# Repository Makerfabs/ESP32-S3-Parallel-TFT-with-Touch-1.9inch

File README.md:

# ESP32-S3-Parallel-TFT-with-Touch-1.9inch

```
/* 
    Version:      V1.1
    Author:       Ricardo
    Create Date:  2023/4/27
*/
```

# Makerfabs

[Makerfabs home page](https://www.makerfabs.com/)

[Makerfabs Wiki](https://wiki.makerfabs.com/)

## Intruduce

Product Link:[ESP32-S3 Parallel TFT with Touch 1.9"](https://www.makerfabs.com/matouch-esp32-s3-parallel-tft-with-touch-1-9-inch.html?search=Esp32%20s3%201.9)

Wiki Link : [ESP32-S3 Parallel 1.9 TFT with Touch](https://wiki.makerfabs.com/ESP32_S3_Parallel_1.9_TFT_with_Touch.html)

IoT applications have a certain demand for the 1.9" screen. The small screen brings higher cost performance and utilization rate. Its main control chip adopts ESP32-S3R8 Dual-core LX7 microcontroller, it features Wifi/ WiFi& Bluetooth 5.0 + BT mesh.

At the same time, it supports battery and USB power supply methods, which brings many possibilities to its application. At the same time, it has a TF card, which can store and transfer sensor data. Also there 2 expansion connectors, with UART/ADC. The colorful display resolution is 320*170, with capacitive touch, which could be a proper solution for IoT applications.

## Features

- Controller: ESP32-S3
- Wireless: WiFi& Bluetooth 5.0
- LCD: 1.9", 320x170 resolution, driver ST7789V2
- LCD interface: 8 bit 8080
- Touch Panel Driver: CST816D
- USB: USB Native, Type-C
- Power Supply: USB Type-C 5.0V(4.0V~5.25V); 3.7V Lipo battery
- Button: Flash button and reset button
- Expansion interface: 2 (UART/ADC)
- MicroSD
- Arduino support
- MicroPython support: Yes
- Operation temperature: -40℃ to +85℃

## Usage

related library versions

- Use type-c use cable connect USB-TTL to PC.
- Select "ESP32-S3 DEV Module"
- Select PSRAM "OPI PSRAM"

"mf_Lvgl" library is modified from Lvgl library (version 8.3.2). 

Please unzip "lib/mf_Lvgl.zip"."TouchLib" and copy to arduino library directory.

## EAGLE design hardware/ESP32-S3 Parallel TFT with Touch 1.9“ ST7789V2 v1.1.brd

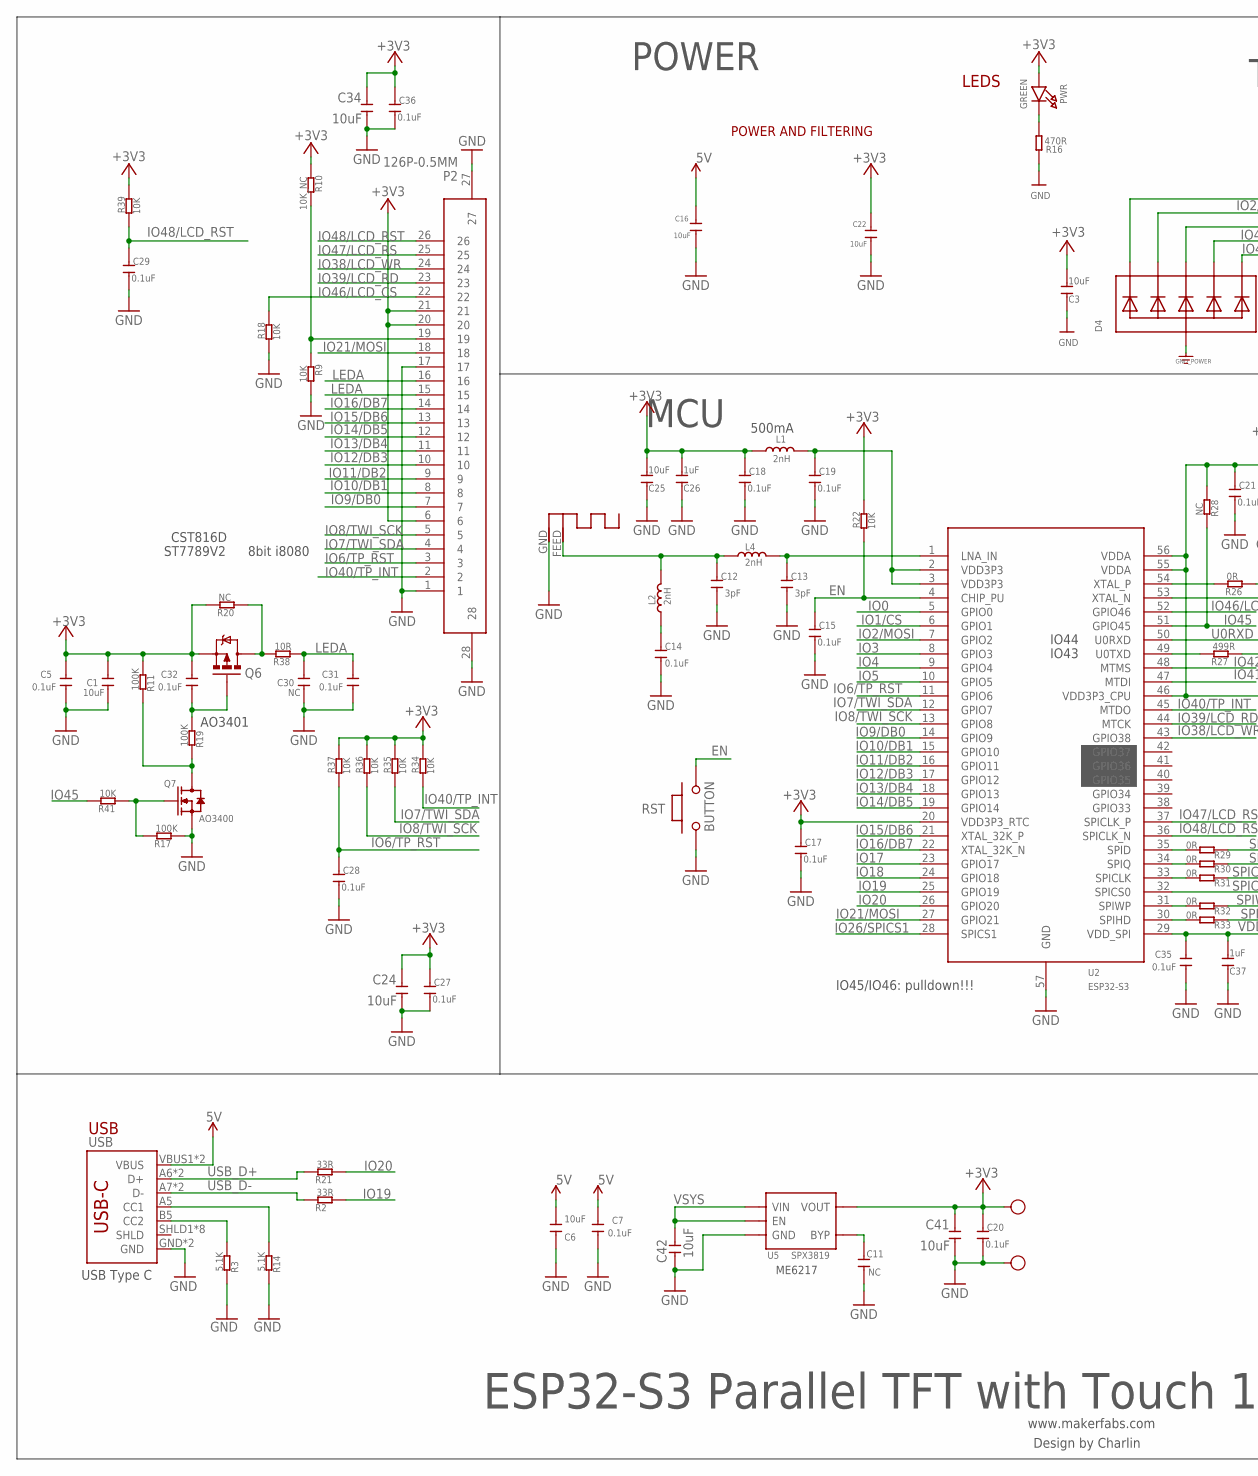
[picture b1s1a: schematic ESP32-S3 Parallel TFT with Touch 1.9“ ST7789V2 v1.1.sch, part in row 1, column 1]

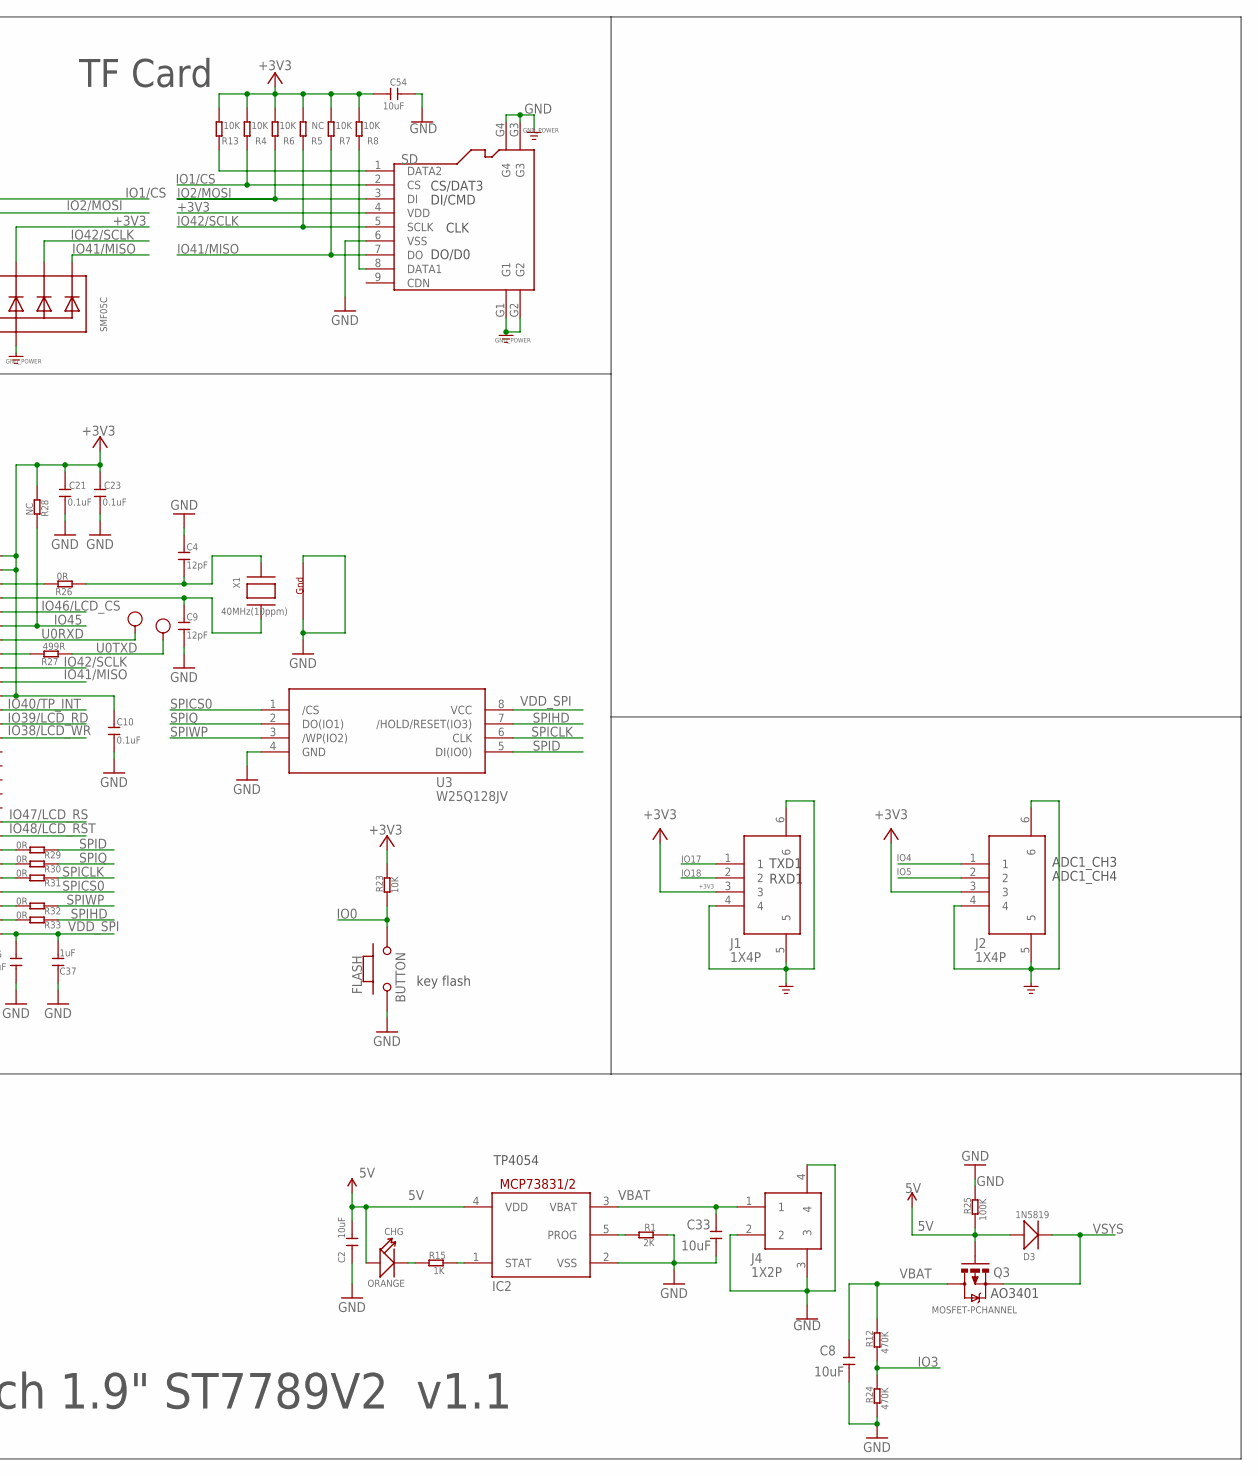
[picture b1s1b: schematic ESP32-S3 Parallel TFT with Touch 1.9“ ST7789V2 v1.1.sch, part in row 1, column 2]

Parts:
ANT1: ANTENNA; RN-ANT
C1, C2, C8, C16, C22, C24, C33, C34, C41, C42: 10uF; 0603
C3, C6, C25, C54: 10uF; DISCRETE_C0603
C4, C9: 12pF; DISCRETE_C0402
C5, C7, C10, C14, C15, C17, C18, C19, C20, C21, C23, C27, C28, C29, C31, C32, C35, C36: 0.1uF; DISCRETE_C0402
C11: NC; DISCRETE_C0402
C12, C13: 3pF; DISCRETE_C0402
C26, C37: 1uF; DISCRETE_C0603
C30: NC; 0603
CHG: ORANGE; D0603
D3: 1N5819; SOD323
D4: SMF05C; SOT363
FLASH: BUTTON; 157SW
G: TEST-POINT'4545'; TP-D45MIL; PARTNO DNP
IC2: MCP73831/OT; SOT23-5L
J1, J2: 1X4P; 1X4P-SMT1.25MM
J4: 1X2P; 1X2P-SMT1.25MM
L1: 2nH; DISCRETE_L0603
L2, L4: 2nH; DISCRETE_L0402
P2: 126P-0.5MM; 1*26P-SMT0.5MM
PWR: GREEN; CHIPLED_0805_NOOUTLINE
Q3, Q6: MOSFET-PCHANNEL; SOT23-3
Q7: AO3400; DISCRETE_SOT23
R1: 2K; DISCRETE_R0402
R2, R21: 33R; DISCRETE_R0402
R3, R14: 5.1K; DISCRETE_R0402
R4, R6, R7, R8, R9, R13, R18, R22, R23, R34, R35, R36, R37, R39, R41: 10K; DISCRETE_R0402
R5, R20, R28: NC; DISCRETE_R0402
R10: 10K_NC; DISCRETE_R0402
R11, R17, R19, R25: 100K; DISCRETE_R0402
R12, R24: 470K; DISCRETE_R0402
R15: 1K; DISCRETE_R0402
R16: 470R; DISCRETE_R0402
R26, R29, R30, R31, R32, R33: 0R; DISCRETE_R0402
R27: 499R; DISCRETE_R0402
R38: 10R; DISCRETE_R0402
RST: BUTTON; 157SW
RX: TEST-POINT'4545'; TP-D45MIL; PARTNO DNP
SD: HOLDER-MICROSD-9P; 9P-SMD-W/-RING
TX: TEST-POINT'4545'; TP-D45MIL; PARTNO DNP
U2: ESP32-S3; QFN56-7*7MM
U3: W25Q128JV; SOIC-8-208MIL
U5: SPX3819; SOT23-5
USB: USB_C5; USB-C-16P-5
V: TEST-POINT'4545'; TP-D45MIL; PARTNO DNP
X1: 40MHz(10ppm); NX3225

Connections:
5V: C2.2, C6.2, C7.2, C16.1, CHG.+, D3.+, IC2.4 (VDD), Q3.1 (G), R25.1, USB.VBUS1 (VBUS), USB.VBUS2 (VBUS)
+3V3: C1.2, C3.2, C5.2, C10.2, C17.2, C18.2, C20.2, C21.2, C22.1, C23.2, C24.2, C25.2, C26.2, C27.2, C32.2, C34.2, C36.2, C41.2, C54.2, D4.4 (C3), J1.3, J2.3, L1.1, P2.6, P2.20, P2.21, PWR.A, Q6.2 (S), R4.2, R5.2, R6.2, R7.2, R8.2, R10.2, R11.1, R13.2, R20.2, R22.2, R23.2, R28.1, R34.2, R35.2, R36.2, R37.2, R39.2, SD.4 (VDD), U2.20 (VDD3P3_RTC), U2.46 (VDD3P3_CPU), U2.55 (VDDA), U2.56 (VDDA), U5.5 (VOUT), V.T
EN: C15.2, R22.1, RST.2, U2.4 (CHIP_PU)
GND: ANT1.GND, C1.1, C2.1, C3.1, C4.2, C5.1, C6.1, C7.1, C8.1, C9.1, C10.1, C11.1, C12.1, C13.1, C14.1, C15.1, C16.2, C17.1, C18.1, C19.1, C20.1, C21.1, C22.2, C23.1, C24.1, C25.1, C26.1, C27.1, C28.1, C29.1, C30.1, C31.1, C33.1, C34.1, C35.1, C36.1, C37.1, C41.1, C42.1, C54.1, D4.2 (A), FLASH.1, G.T, IC2.2 (VSS), J1.4, J1.5, J1.6, J2.4, J2.5, J2.6, J4.2, J4.3, J4.4, P2.1, P2.17, P2.27, P2.28, Q7.2 (S), R1.2, R3.2, R9.1, R14.2, R16.1, R17.1, R18.1, R24.1, R25.2, RST.1, SD.6 (VSS), SD.G1, SD.G2, SD.G3, SD.G4, U2.57 (GND), U3.4 (GND), U5.2 (GND), USB.GND, USB.GND2 (GND), X1.2 (G2), X1.4 (G1)
IO0: FLASH.2, R23.1, U2.5 (GPIO0)
IO1/CS: D4.1 (C1), R4.1, SD.2 (CS), U2.6 (GPIO1)
IO2/MOSI: D4.3 (C2), R6.1, SD.3 (DI), U2.7 (GPIO2)
IO3: R12.1, R24.2, U2.8 (GPIO3)
IO4: J2.1, U2.9 (GPIO4)
IO5: J2.2, U2.10 (GPIO5)
IO6/TP_RST: C28.2, P2.3, R37.1, U2.11 (GPIO6)
IO7/TWI_SDA: P2.4, R35.1, U2.12 (GPIO7)
IO8/TWI_SCK: P2.5, R36.1, U2.13 (GPIO8)
IO9/DB0: P2.7, U2.14 (GPIO9)
IO10/DB1: P2.8, U2.15 (GPIO10)
IO11/DB2: P2.9, U2.16 (GPIO11)
IO12/DB3: P2.10, U2.17 (GPIO12)
IO13/DB4: P2.11, U2.18 (GPIO13)
IO14/DB5: P2.12, U2.19 (GPIO14)
IO15/DB6: P2.13, U2.21 (XTAL_32K_P)
IO16/DB7: P2.14, U2.22 (XTAL_32K_N)
IO17: J1.1, U2.23 (GPIO17)
IO18: J1.2, U2.24 (GPIO18)
IO19: R2.1, U2.25 (GPIO19)
IO20: R21.1, U2.26 (GPIO20)
IO21/MOSI: P2.18, U2.27 (GPIO21)
IO26/SPICS1: U2.28 (SPICS1)
IO38/LCD_WR: P2.24, U2.43 (GPIO38)
IO39/LCD_RD: P2.23, U2.44 (MTCK)
IO40/TP_INT: P2.2, R34.1, U2.45 (MTDO)
IO41/MISO: D4.6 (C5), R7.1, SD.7 (DO), U2.47 (MTDI)
IO42/SCLK: D4.5 (C4), R5.1, SD.5 (SCLK), U2.48 (MTMS)
IO45: R28.2, R41.2, U2.51 (GPIO45)
IO46/LCD_CS: P2.22, R18.2, U2.52 (GPIO46)
IO47/LCD_RS: P2.25, U2.37 (SPICLK_P)
IO48/LCD_RST: C29.2, P2.26, R39.1, U2.36 (SPICLK_N)
LEDA: C30.2, C31.2, P2.15, P2.16, R38.1
unnamed: IC2.5 (PROG), R1.1
unnamed: C32.1, Q6.1 (G), R19.1
unnamed: R14.1, USB.A5 (CC1)
unnamed: PWR.C, R16.2
unnamed: P2.19, R9.2, R10.1
unnamed: Q6.3 (D), R20.1, R38.2
unnamed: R3.1, USB.B5 (CC2)
unnamed: Q7.3 (D), R11.2, R19.2
unnamed: Q7.1 (G), R17.2, R41.1
unnamed: CHG.-, R15.1
unnamed: IC2.1 (STAT), R15.2
unnamed: ANT1.FEED, C12.2, L2.2, L4.1
unnamed: C13.2, L4.2, U2.1 (LNA_IN)
unnamed: R29.2, U2.35 (SPID)
unnamed: C19.2, L1.2, U2.2 (VDD3P3), U2.3 (VDD3P3)
unnamed: C14.2, L2.1
unnamed: R30.2, U2.34 (SPIQ)
unnamed: R26.2, U2.54 (XTAL_P)
unnamed: R31.2, U2.33 (SPICLK)
unnamed: R32.2, U2.31 (SPIWP)
unnamed: R33.2, U2.30 (SPIHD)
unnamed: R13.1, SD.1 (DATA2)
unnamed: R8.1, SD.8 (DATA1)
unnamed: R27.2, U2.49 (U0TXD)
unnamed: C9.2, U2.53 (XTAL_N), X1.3 (X2)
unnamed: C4.1, R26.1, X1.1 (X1)
unnamed: C11.2, U5.4 (BYP)
SPICLK: R31.1, U3.6 (CLK)
SPICS0: U2.32 (SPICS0), U3.1 (/CS)
SPID: R29.1, U3.5 (DI(IO0))
SPIHD: R33.1, U3.7 (/HOLD/RESET(IO3))
SPIQ: R30.1, U3.2 (DO(IO1))
SPIWP: R32.1, U3.3 (/WP(IO2))
U0RXD: RX.T, U2.50 (U0RXD)
U0TXD: R27.1, TX.T
USB_D+: R21.2, USB.A6 (D+), USB.B6 (D+)
USB_D-: R2.2, USB.A7 (D-), USB.B7 (D-)
VBAT: C8.2, C33.2, IC2.3 (VBAT), J4.1, Q3.3 (D), R12.2
VDD_SPI: C35.2, C37.2, U2.29 (VDD_SPI), U3.8 (VCC)
VSYS: C42.2, D3.-, Q3.2 (S), U5.1 (VIN), U5.3 (EN)

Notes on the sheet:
www.makerfabs.com
Design by Charlin
LEDS
POWER AND FILTERING
key flash
ESP32-S3 Parallel TFT with Touch 1.9" ST7789V2 v1.1
POWER
TF Card
USB
USB Type C
MCU
500mA
ME6217
ADC1_CH3
ADC1_CH4
TP4054
AO3401
TXD1
RXD1
8bit i8080
IO45/IO46: pulldown!!!
IO43
IO44
CST816D
ST7789V2
CS/DAT3
DI/CMD
DO/D0
CLK

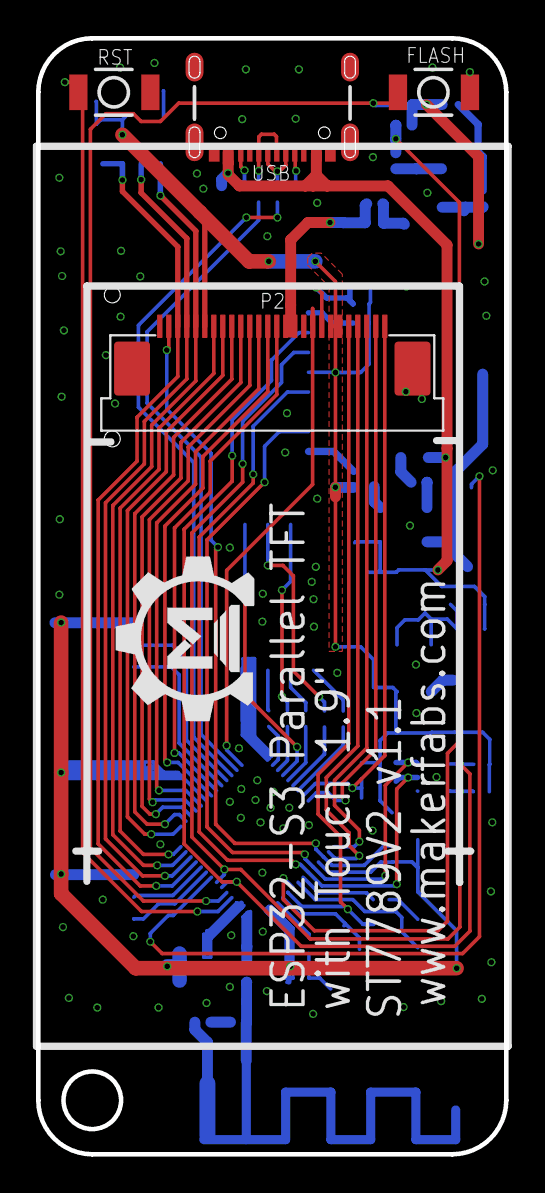
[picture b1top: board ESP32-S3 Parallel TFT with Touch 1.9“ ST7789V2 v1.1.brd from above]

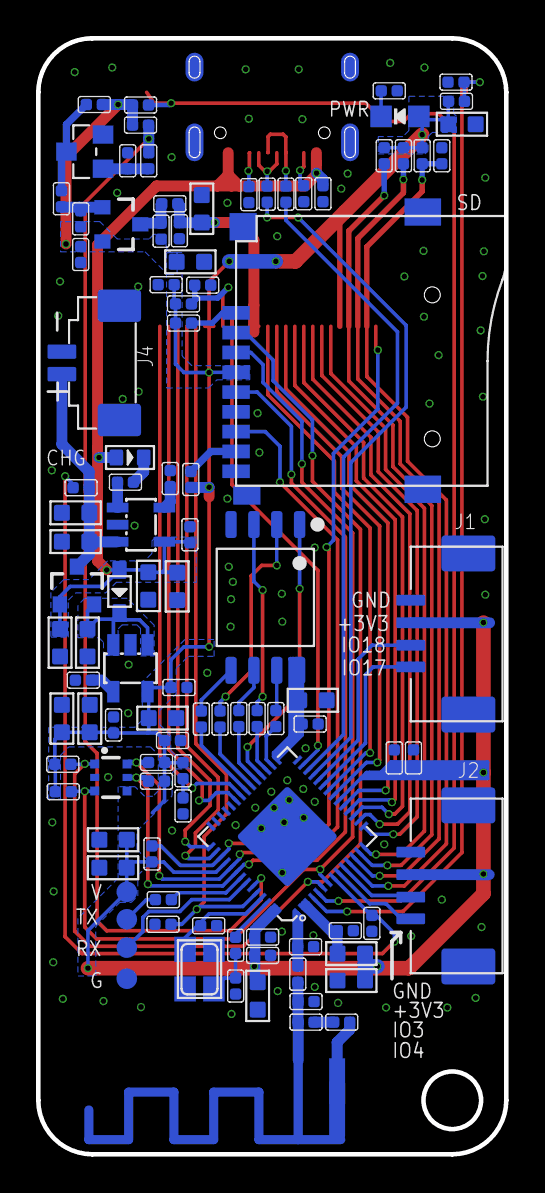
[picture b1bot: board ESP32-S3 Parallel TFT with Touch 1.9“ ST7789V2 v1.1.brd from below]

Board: 2 copper layers, 26.0 x 62.0 mm, 109 parts (104 on the bottom side), 76 nets.

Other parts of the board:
U$1: MAKERFABS_0.3

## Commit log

2023-04-27 hardware upload
2023-04-29 Add firmware
2023-05-08 related library versions
2023-05-08 update the readme
2023-05-09 Add 2 lvgl demo
2023-05-09 Add squareline demo
2023-05-09 Edit readme

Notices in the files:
parts and their libraries:
microbuilder: This work is placed in the public domain, and may be freely used for commercial and non-commercial work with the following conditions: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
User-Submitted: Licensing: Creative Commons ShareAlike 4.0 International - https://creativecommons.org/licenses/by-sa/4.0
